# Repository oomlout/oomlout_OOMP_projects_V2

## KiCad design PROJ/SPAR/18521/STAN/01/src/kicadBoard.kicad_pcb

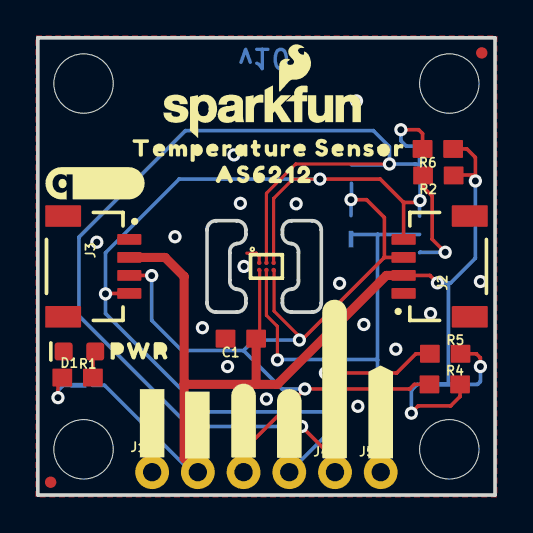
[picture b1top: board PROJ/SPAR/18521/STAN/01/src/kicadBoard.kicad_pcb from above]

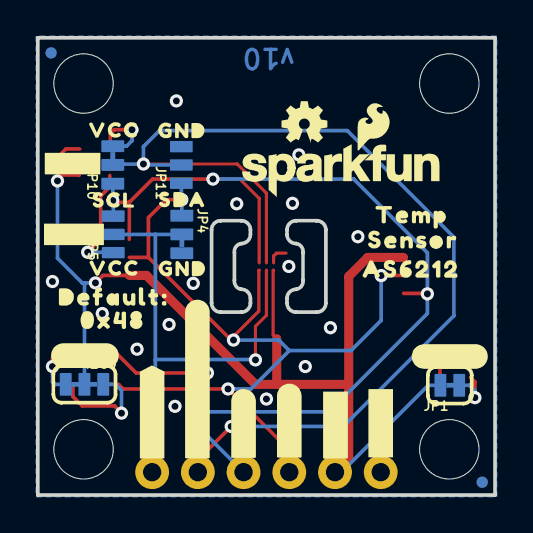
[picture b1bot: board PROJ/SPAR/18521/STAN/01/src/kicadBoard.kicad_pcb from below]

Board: 2 copper layers, 25.4 x 25.4 mm, 62 parts (31 on the bottom side), 12 nets.

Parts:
C1: 0.1uF; 0603
D1: RED; LED-0603
FD1, FD2, FD3, FD4: FIDUCIALUFIDUCIAL; FIDUCIAL-MICRO
FRAME1: FRAME-LETTER; CREATIVE_COMMONS
I2C0: SMT-JUMPER_3_2-NC_TRACE_SILK
J1: PTH; 1X04_NO_SILK
J2, J3: QWIIC_RA; JST04_1MM_RA
J4, J5: 1X01_NO_SILK
JP1: LED; SMT-JUMPER_2_NC_TRACE_SILK
JP2, JP3, JP8, JP9: STAND-OFF
JP4, JP10: JUMPER-SMT_3_1-NC_TRACE_NO-SILK; SMT-JUMPER_3_1-NC_TRACE_NO-SILK
JP5, JP11: JUMPER-SMT_3_NO_NO_SILK; SMT-JUMPER_3_0-NO_TRACE_NO-SILK
LOGO1: OSHW-LOGOMINI; OSHW-LOGO-MINI
LOGO2, LOGO4: SFE_LOGO_NAME_FLAME.1_INCH; SFE_LOGO_NAME_FLAME_.1
R1: 1k; 0603
R2, R6: 10k; 0603
R4, R5: 2.2k; 0603
U2: AS6212; WLCSP
U$1: #LED#10
U$2: #I2C#11
U$3, U$25: AS62128
U$4: #AD0#1
U$5: #AD1#1
U$6: SCL3
U$7, U$13: VCC4
U$8: DEFAULT#11
U$9, U$14: GND5
U$10: SDA6
U$11, U$12: #ALRT#AD1#12
U$15: QWIIC_5.5MM
U$16: SENSOR8
U$17: TEMP9
U$18: 0X4812
U$19: PWR12
U$20, U$21: #3V3#13
U$24: TEMPERATURE_SENSOR7
U$26, U$30: #GND#62130
U$28, U$34: #SDA#62131
U$29, U$35: #SCL#62132
U$31, U$36: #ADD0#0

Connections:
3.3V: C1.1, I2C0.2, J1.2, J2.2, J3.2, JP1.2, R2.1, R6.1, U2.B1
ADD0: J5.1, JP4.2, JP5.2, U2.B2
ALERT/ADD1: J4.1, JP10.2, JP11.2, U2.A2
GND: C1.2, D1.C, J1.1, J2.1, J3.1, JP4.3, JP11.3, U2.A1
unnamed: D1.A, R1.2
unnamed: I2C0.1, R5.2
unnamed: I2C0.3, R4.2
unnamed: JP10.3, R6.2
unnamed: JP5.1, R2.2
unnamed: JP1.1, R1.1
SCL: J1.4, J2.4, J3.4, JP5.3, JP10.1, R5.1, U2.A3
SDA: J1.3, J2.3, J3.3, JP4.1, JP11.1, R4.1, U2.B3

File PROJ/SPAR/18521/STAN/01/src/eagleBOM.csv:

"Part";"Value";"Device";"Package";"Description";"PROD_ID";"VALUE";
"C1";"0.1uF";"0.1UF-0603-25V-(+80/-20%)";"0603";"0.1µF ceramic capacitors";"CAP-00810";"0.1uF";
"D1";"RED";"LED-RED0603";"LED-0603";"Red SMD LED";"DIO-00819";"RED";
"FD1";"FIDUCIALUFIDUCIAL";"FIDUCIALUFIDUCIAL";"FIDUCIAL-MICRO";"Fiducial Alignment Points";"";"";
"FD2";"FIDUCIALUFIDUCIAL";"FIDUCIALUFIDUCIAL";"FIDUCIAL-MICRO";"Fiducial Alignment Points";"";"";
"FD3";"FIDUCIALUFIDUCIAL";"FIDUCIALUFIDUCIAL";"FIDUCIAL-MICRO";"Fiducial Alignment Points";"";"";
"FD4";"FIDUCIALUFIDUCIAL";"FIDUCIALUFIDUCIAL";"FIDUCIAL-MICRO";"Fiducial Alignment Points";"";"";
"FRAME1";"FRAME-LETTER";"FRAME-LETTER";"CREATIVE_COMMONS";"Schematic Frame - Letter";"";"";
"I2C";"";"JUMPER-SMT_3_2-NC_TRACE_SILK";"SMT-JUMPER_3_2-NC_TRACE_SILK";"Normally closed trace jumper (2 of 2 connections)";"";"";
"J1";"PTH";"I2C_STANDARD_NO_SILK";"1X04_NO_SILK";"SparkFun I2C Standard Pinout Header";"";"";
"J2";"QWIIC_RA";"QWIIC_CONNECTORJS-1MM";"JST04_1MM_RA";"SparkFun I2C Standard Qwiic Connector";"CONN-13694";"QWIIC_RIGHT_ANGLE";
"J3";"QWIIC_RA";"QWIIC_CONNECTORJS-1MM";"JST04_1MM_RA";"SparkFun I2C Standard Qwiic Connector";"CONN-13694";"QWIIC_RIGHT_ANGLE";
"J4";"";"CONN_01PTH_NO_SILK_YES_STOP";"1X01_NO_SILK";"Single connection point. Often used as Generic Header-pin footprint for 0.1 inch spaced/style header connections";"";"";
"J5";"";"CONN_01PTH_NO_SILK_YES_STOP";"1X01_NO_SILK";"Single connection point. Often used as Generic Header-pin footprint for 0.1 inch spaced/style header connections";"";"";
"JP1";"LED";"JUMPER-SMT_2_NC_TRACE_SILK";"SMT-JUMPER_2_NC_TRACE_SILK";"Normally closed trace jumper";"";"";
"JP2";"STAND-OFF";"STAND-OFF";"STAND-OFF";"Stand Off";"";"";
"JP3";"STAND-OFF";"STAND-OFF";"STAND-OFF";"Stand Off";"";"";
"JP4";"JUMPER-SMT_3_1-NC_TRACE_NO-SILK";"JUMPER-SMT_3_1-NC_TRACE_NO-SILK";"SMT-JUMPER_3_1-NC_TRACE_NO-SILK";"Normally closed trace jumper (1 of 2 connections)";"";"";
"JP5";"JUMPER-SMT_3_NO_NO_SILK";"JUMPER-SMT_3_NO_NO_SILK";"SMT-JUMPER_3_0-NO_TRACE_NO-SILK";"Normally open jumper";"";"";
"JP8";"STAND-OFF";"STAND-OFF";"STAND-OFF";"Stand Off";"";"";
"JP9";"STAND-OFF";"STAND-OFF";"STAND-OFF";"Stand Off";"";"";
"JP10";"JUMPER-SMT_3_1-NC_TRACE_NO-SILK";"JUMPER-SMT_3_1-NC_TRACE_NO-SILK";"SMT-JUMPER_3_1-NC_TRACE_NO-SILK";"Normally closed trace jumper (1 of 2 connections)";"";"";
"JP11";"JUMPER-SMT_3_NO_NO_SILK";"JUMPER-SMT_3_NO_NO_SILK";"SMT-JUMPER_3_0-NO_TRACE_NO-SILK";"Normally open jumper";"";"";
"LOGO1";"OSHW-LOGOMINI";"OSHW-LOGOMINI";"OSHW-LOGO-MINI";"Open-Source Hardware (OSHW) Logo";"";"";
"LOGO4";"SFE_LOGO_NAME_FLAME.1_INCH";"SFE_LOGO_NAME_FLAME.1_INCH";"SFE_LOGO_NAME_FLAME_.1";"SparkFun Font Logo w/ Flame";"";"";
"R1";"1k";"1KOHM-0603-1/10W-1%";"0603";"1kΩ resistor";"RES-07856";"1k";
"R2";"10k";"10KOHM-0603-1/10W-1%";"0603";"10kΩ resistor";"RES-00824";"10k";
"R4";"2.2k";"2.2KOHM-0603-1/10W-1%";"0603";"2.2kΩ resistor";"RES-08272";"2.2k";
"R5";"2.2k";"2.2KOHM-0603-1/10W-1%";"0603";"2.2kΩ resistor";"RES-08272";"2.2k";
"R6";"10k";"10KOHM-0603-1/10W-1%";"0603";"10kΩ resistor";"RES-00824";"10k";
"U2";"AS6212";"AS6212WLCSP";"WLCSP";"AMS AS6212 Low-Power Digital Temperature Sensor";"IC-16171";"AS6212";

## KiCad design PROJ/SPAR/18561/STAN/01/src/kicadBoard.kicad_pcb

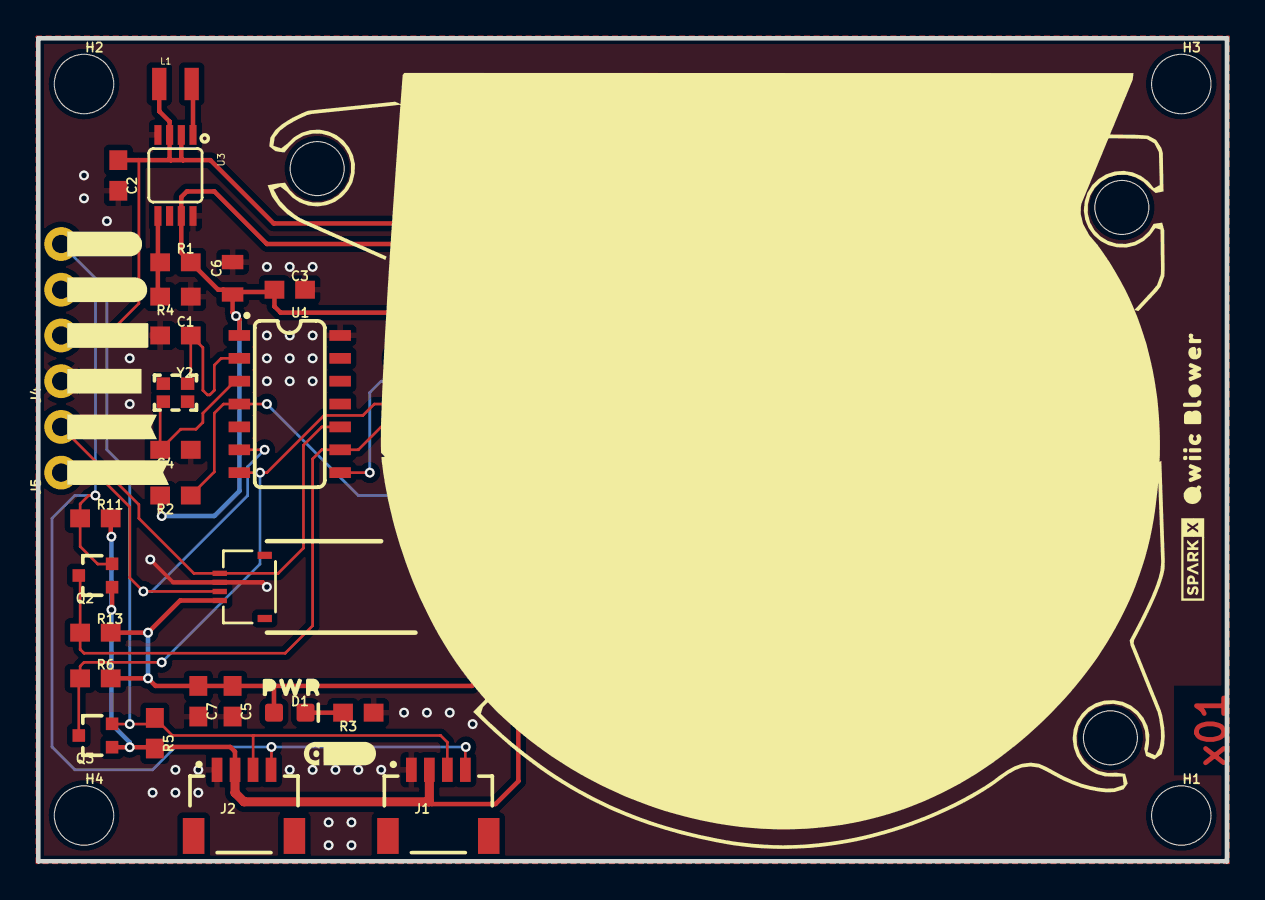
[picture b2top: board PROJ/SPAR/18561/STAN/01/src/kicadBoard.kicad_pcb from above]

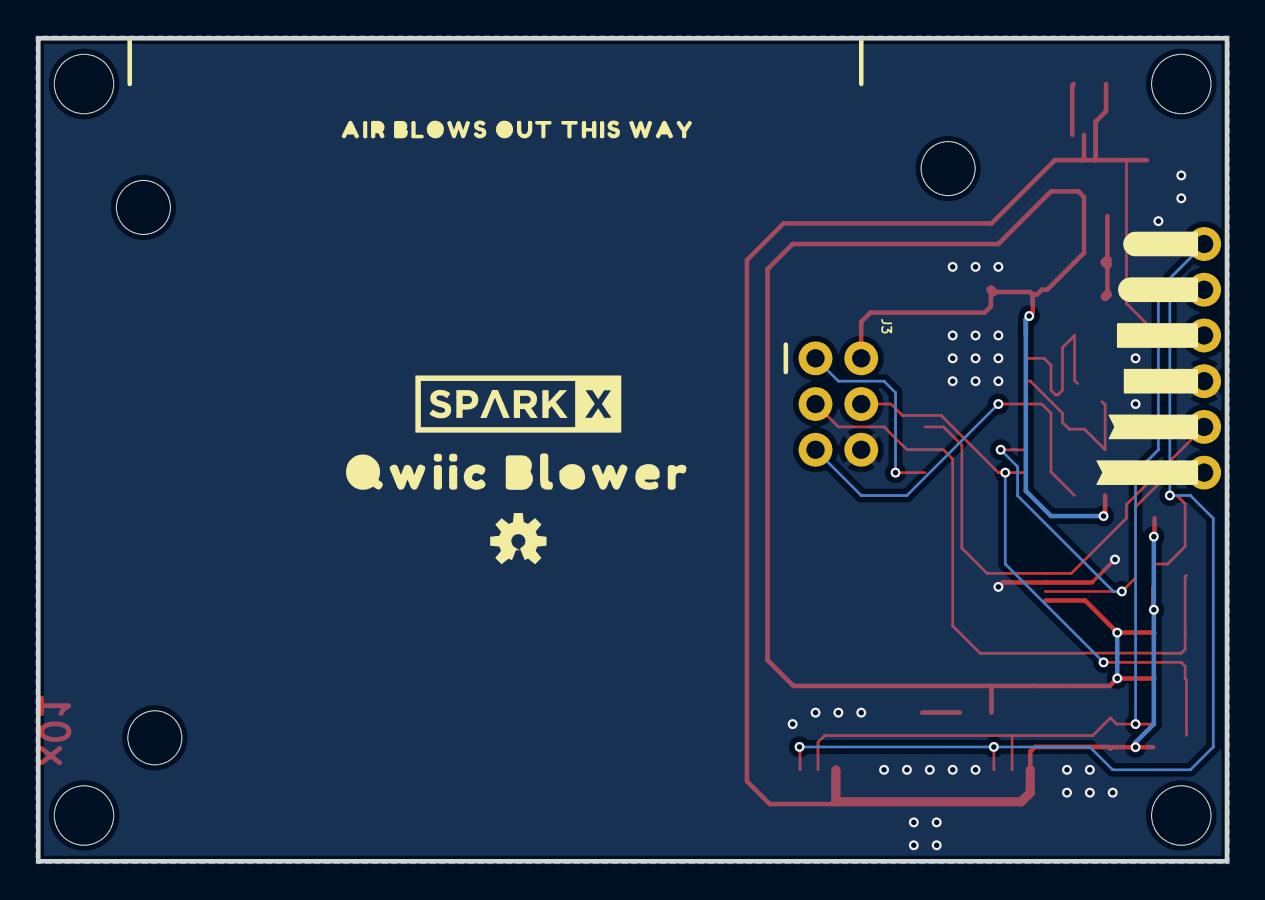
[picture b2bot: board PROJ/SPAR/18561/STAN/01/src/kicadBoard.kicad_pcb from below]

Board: 2 copper layers, 66.0 x 45.7 mm, 53 parts (11 on the bottom side), 16 nets.

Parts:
C1, C4: 22pF; 0603
C2: 10uF; 0603
C3, C5: 0.1uF; 0603
C6: 22uF; 0805
C7: 1.0uF; 0603
D1: RED; LED-0603
FRAME1: FRAME-LETTER; CREATIVE_COMMONS
H1, H2, H3, H4: STAND-OFF
J1, J2: QWIIC_RIGHT_ANGLE; JST04_1MM_RA
J3: AVR_SPI_PROG_3X2NS; 2X3-NS
J4: 1X04_NO_SILK
J5: 1X02_NO_SILK
L1: 2.2μH; 0806
Q2, Q3: 310mA/60V/1.6Ω; SOT323
R1: 750K; 0603
R2: 10k; 0603
R3: 1k; 0603
R4: 100k; 0603
R5, R6, R11, R13: 2.2k; 0603
U1: ATtiny841; SO14
U3: PAM2401; MSOP8
U$1: #_TACH#0
U$2: #_PWM#0
U$3: #_GND#0
U$4: #_3#3V#0
U$5: #_SDA#0
U$6: #_SCL#0
U$7: #SCL_#0
U$8: #SDA_#0
U$9: #3#3V_#0
U$10: #GND_#0
U$11: #PWM_#0
U$12: #TACH_#0
U$13: QWIIC_4MM
U$14: QWIIC_BLOWER0
U$15: SPARKX-TINY
U$16: AIR_BLOWS_OUT_THIS_WAY0
U$17: _QWIIC_BLOWER_0
U$18: SPARKX-LARGE
U$19: NINTENDO_SWITCH_FAN; FPC_4_0.5MM
U$20: OSHW-LOGO-S
U$21: PWR0
Y2: 16MHz; CRYSTAL-SMD-2.0X1.6MM

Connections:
3.3V: C2.1, J1.2, J2.2, J4.2, L1.1, Q2.1, Q3.1, R5.2, R11.2, U3.2, U3.3
5V: C3.1, C5.1, C6.1, C7.1, D1.A, J3.2, R1.2, R2.2, R6.2, R13.2, U1.1, U3.7, U$19.1
25KHZ_PWM: J5.2, U1.10, U$19.4
CIPO: J3.1, U1.8
FAN_TACH: J5.1, U1.6, U$19.2
GND: C1.1, C2.2, C3.2, C4.1, C5.2, C6.2, C7.2, J1.1, J2.1, J3.6, J4.1, R3.1, R4.1, U1.14, U3.4, U3.8, U$19.3
HV_SCL: J3.3, Q2.3, R13.1, U1.9
HV_SDA: J3.4, Q3.3, R6.1, U1.7
unnamed: C4.2, U1.3, Y2.1
unnamed: R1.1, R4.2, U3.5
unnamed: L1.2, U3.1
unnamed: C1.2, U1.2, Y2.3
unnamed: D1.C, R3.2
SCL: J1.4, J2.4, J4.4, Q2.2, R11.1
SDA: J1.3, J2.3, J4.3, Q3.2, R5.1
~RST: J3.5, R2.1, U1.4

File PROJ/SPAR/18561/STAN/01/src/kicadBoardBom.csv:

"Id";"Designator";"Package";"Quantity";"Designation";"Supplier and ref";
1;"R3";"0603";1;"1k";;;
2;"C6";"0805";1;"22uF";;;
3;"H3,H4,H2,H1";"STAND-OFF";4;"STAND-OFF";;;
4;"R5,R6,R11,R13";"0603";4;"2.2k";;;
5;"D1";"LED-0603";1;"RED";;;
6;"U$5";"#_SDA#0";1;"";;;
7;"C3,C5";"0603";2;"0.1uF";;;
8;"Q2,Q3";"SOT323";2;"310mA/60V/1.6Ω";;;
9;"Y2";"CRYSTAL-SMD-2.0X1.6MM";1;"16MHz";;;
10;"C2";"0603";1;"10uF";;;
11;"R1";"0603";1;"750K";;;
12;"U$6";"#_SCL#0";1;"";;;
13;"U$13";"QWIIC_4MM";1;"";;;
14;"J2,J1";"JST04_1MM_RA";2;"QWIIC_RIGHT_ANGLE";;;
15;"U$14";"QWIIC_BLOWER0";1;"";;;
16;"L1";"0806";1;"2.2μH";;;
17;"U1";"SO14";1;"ATtiny841";;;
18;"U3";"MSOP8";1;"PAM2401";;;
19;"U$15";"SPARKX-TINY";1;"";;;
20;"U$2";"#_PWM#0";1;"";;;
21;"C7";"0603";1;"1.0uF";;;
22;"C1,C4";"0603";2;"22pF";;;
23;"R4";"0603";1;"100k";;;
24;"U$1";"#_TACH#0";1;"";;;
25;"U$3";"#_GND#0";1;"";;;
26;"U$19";"FPC_4_0.5MM";1;"NINTENDO_SWITCH_FAN";;;
27;"R2";"0603";1;"10k";;;
28;"J5";"1X02_NO_SILK";1;"";;;
29;"U$4";"#_3#3V#0";1;"";;;
30;"U$21";"PWR0";1;"";;;
31;"FRAME1";"CREATIVE_COMMONS";1;"FRAME-LETTER";;;
32;"J4";"1X04_NO_SILK";1;"";;;
33;"U$9";"#3#3V_#0";1;"";;;
34;"U$12";"#TACH_#0";1;"";;;
35;"U$20";"OSHW-LOGO-S";1;"";;;
36;"J3";"2X3-NS";1;"AVR_SPI_PROG_3X2NS";;;
37;"U$10";"#GND_#0";1;"";;;
38;"U$8";"#SDA_#0";1;"";;;
39;"U$18";"SPARKX-LARGE";1;"";;;
40;"U$11";"#PWM_#0";1;"";;;
41;"U$17";"_QWIIC_BLOWER_0";1;"";;;
42;"U$16";"AIR_BLOWS_OUT_THIS_WAY0";1;"";;;
43;"U$7";"#SCL_#0";1;"";;;

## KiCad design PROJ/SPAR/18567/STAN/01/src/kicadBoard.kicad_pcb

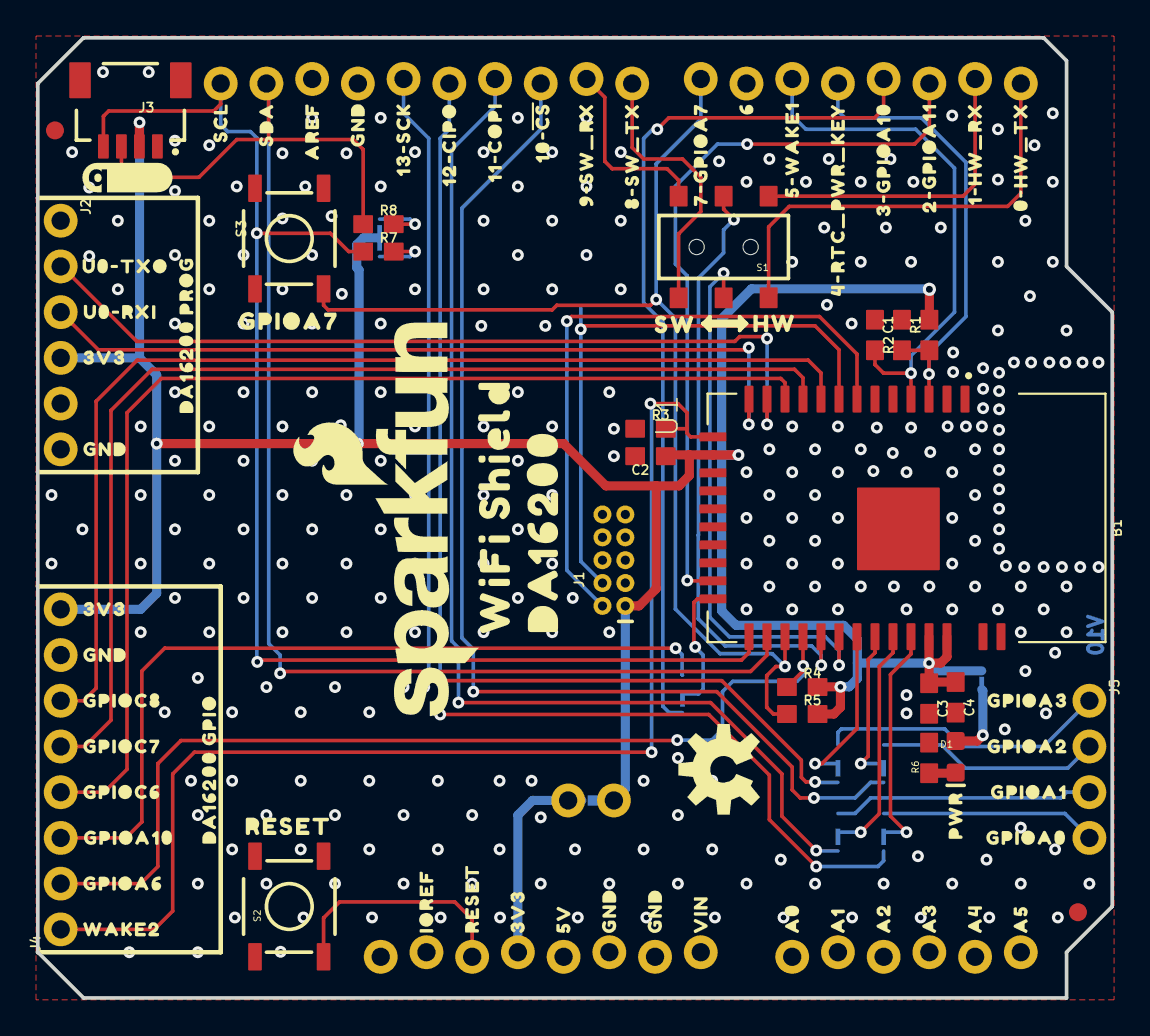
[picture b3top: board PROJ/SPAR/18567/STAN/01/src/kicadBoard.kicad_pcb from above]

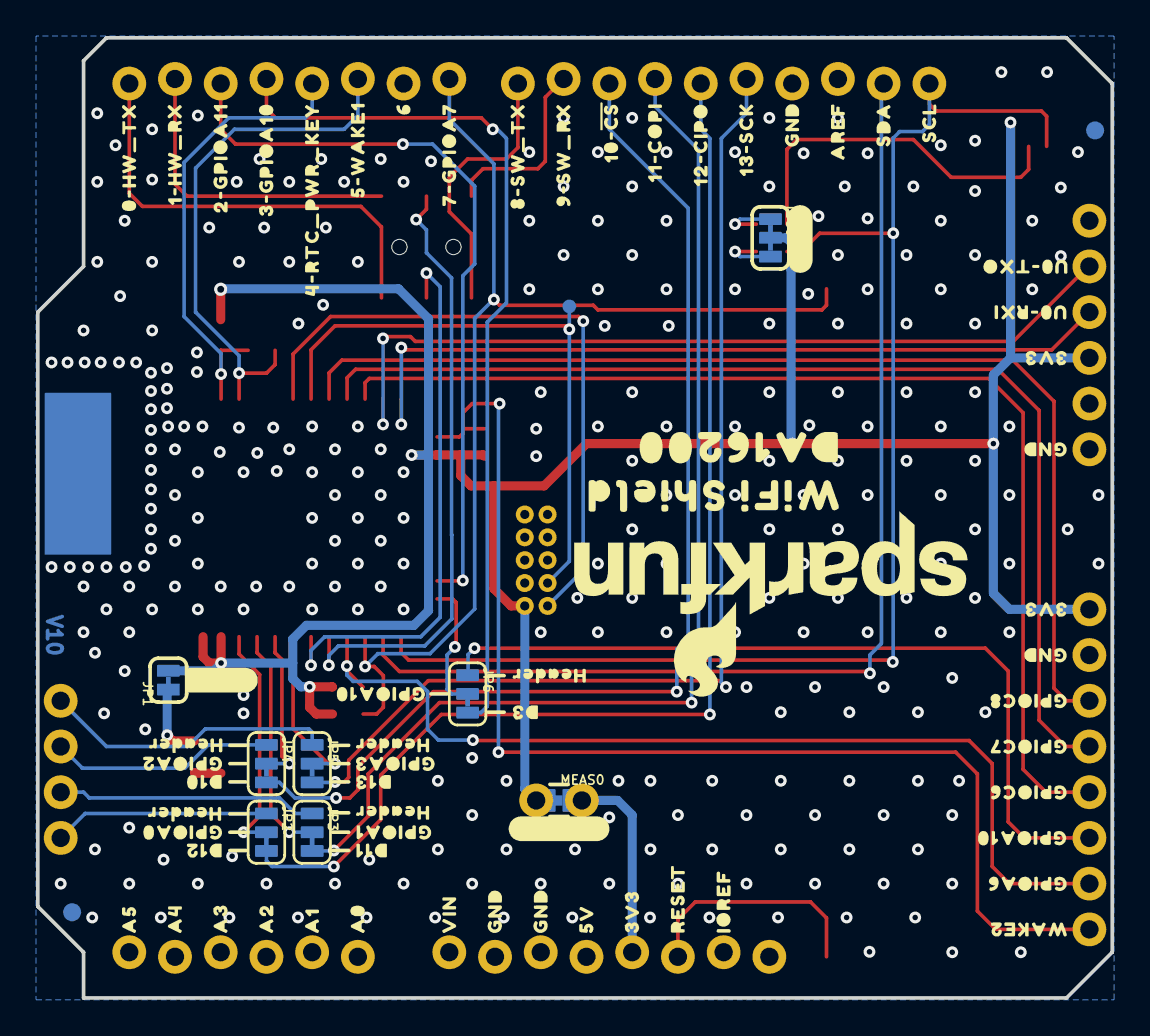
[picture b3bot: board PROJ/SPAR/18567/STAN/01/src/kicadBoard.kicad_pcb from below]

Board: 2 copper layers, 59.7 x 53.3 mm, 160 parts (75 on the bottom side), 44 nets.

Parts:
B1: ARDUINO_UNO_R3_SHIELD; UNO_R3_SHIELD_NOLABELS_LOCK
C1: DNP; 0603
C2, C3: 1uF; 0603
C4: 10uF; 0603
D1: RED; LED-0603
FD1, FD2, FD3, FD4: FIDUCIAL1X2; FIDUCIAL-1X2
FRAME1: FRAME-LETTER; CREATIVE_COMMONS
I2C0: SMT-JUMPER_3_2-NC_TRACE_SILK
J1: CORTEX_JTAG_DEBUG; 2X5-PTH-1.27MM-NO_SILK
J2: 1X06_NO_SILK
J3: QWIIC_RA; JST04_1MM_RA
J4: 1X08_NO_SILK
J5: 1X04_NO_SILK
JP1: SMT-JUMPER_2_NC_TRACE_SILK
JP2, JP3, JP4, JP5, JP6: SMT-JUMPER_3_1-NC_TRACE_SILK
LOGO1, LOGO3: SFE_LOGO_NAME_FLAME.2_INCH; SFE_LOGO_NAME_FLAME_.2
LOGO2: OSHW-LOGOM; OSHW-LOGO-M
LOGO4: QWIIC_LOGO_5MM; QWIIC_5MM
MEAS0: COMBO-JUMPER_2_NC_TRACE
R1: DNP; 0603
R2, R3, R4, R5, R7, R8: 4.7k; 0603
R6: 200; 0603
S1: DPDT; SWITCH_DPDT_SMD_AYZ0202
S2: Reset; TACTILE_SWITCH_SMD_5.2MM
S3: TACTILE_SWITCH_SMD_5.2MM
TP1: PAD.03X.03
U1: DA16200MOD; XCVR_DA16200MOD-AAC4WA32
U$1, U$16: IOREF0
U$2, U$19: RESET0
U$3, U$37, U$39, U$41, U$85, U$87: 3V30
U$4, U$55: 5V0
U$5, U$6, U$28, U$40, U$52, U$56, U$57, U$79, U$86, U$88: GND0
U$7, U$58: VIN0
U$8, U$59: A00
U$9, U$60: A10
U$10, U$61: A20
U$11, U$62: A30
U$12, U$63: A40
U$13, U$64: A50
U$14, U$65: 0#HW_TX0
U$15, U$66: 1#HW_RX0
U$17, U$95: GPIOA60
U$18, U$70: 4#RTC_PWR_KEY0
U$20, U$73: 8#SW_TX0
U$21, U$72: 7#GPIOA70
U$23, U$33: 5#WAKE10
U$24, U$75: 10##CS#0
U$25, U$76: 11#COPI0
U$26, U$77: 12#CIPO0
U$27, U$78: 13#SCK0
U$29, U$80: AREF0
U$30, U$81: SDA0
U$31, U$82: SCL0
U$32, U$74: 9#SW_RX0
U$34: GPIOA70
U$35, U$48: WAKE20
U$36: RESET_0
U$38, U$71: 60
U$42: HW0
U$43: SW0
U$44, U$89: GPIOC80
U$45, U$90: GPIOC70
U$46, U$91: GPIOC60
U$47, U$69, U$92: GPIOA100
U$49: #I2C#0
U$50, U$109: 2#GPIOA110
U$51, U$68: 3#GPIOA100
U$53, U$83: U0#TXO0
U$54, U$84: U0#RXI0
U$93, U$115: GPIOA00
U$94, U$114: GPIOA10
U$96: D30
U$97: #LED#0
U$98: #MEAS#0
U$99: PWR0
U$100, U$107: WIFI_SHIELD0
U$101, U$108: DA162000
U$102, U$116: GPIOA20
U$103, U$117: GPIOA30
U$104: DA16200_GPIO0
U$105: DA16200_PROG0
U$106, U$118, U$119, U$120, U$121: HEADER0
U$122: D100
U$123: D110
U$124: D120
U$125: D130

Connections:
3.3V: C2.1, C3.1, C4.1, I2C0.2, J1.1, J2.4, J3.2, J4.8, JP1.2, MEAS0.1, MEAS0.3, R1.2, R4.2, R5.2, U1.15, U1.34, U1.35
ARD_GPIOA10: B1.D3, JP6.3
ARD_HW_RX: B1.RX, S1.1
ARD_HW_TX: B1.TX, S1.4
ARD_RESET: B1.RES, S2.3
ARD_SCL: B1.SCL, J3.4, R7.1, U1.24
ARD_SDA: B1.SDA, J3.3, R8.1, U1.25
ARD_SW_RX: B1.D8, S1.3
ARD_SW_TX: B1.D9, S1.6
GND: B1.GND@0, B1.GND@1, B1.GND@2, C1.2, C2.2, C3.2, C4.2, J1.3, J1.5, J1.9, J2.6, J3.1, J4.7, R2.1, R3.1, R6.2, S2.1, S3.1, U1.2, U1.ANT_GND, U1.GND
GPIOA0: JP2.2, U1.33
GPIOA1: JP3.2, U1.32
GPIOA2: JP4.2, U1.31
GPIOA3: JP5.2, U1.30
GPIOA7: B1.D7, R5.1, S3.3, U1.26
GPIOA10: JP6.2, U1.23
GPIOA11: B1.D2, U1.22
HDR_GPIOA0: J5.4, JP2.1
HDR_GPIOA1: J5.3, JP3.1
HDR_GPIOA2: J5.2, JP4.1
HDR_GPIOA3: J5.1, JP5.1
HDR_GPIOA6: J4.2, R4.1, U1.27
HDR_GPIOA10: J4.3, JP6.1
HDR_GPIOC6: J4.4, U1.11
HDR_GPIOC7: J4.5, U1.10
HDR_GPIOC8: J4.6, U1.9
HDR_RTC_WAKE2: J4.1, R3.2, U1.14
unnamed: B1.3.3V, MEAS0.2, MEAS0.4
unnamed: D1.A, JP1.1
unnamed: I2C0.3, R7.2
unnamed: I2C0.1, R8.2
unnamed: D1.C, R6.1
RTC_PWR_KEY: B1.D4, C1.1, R1.1, U1.3
RTC_WAKE1: B1.D5, R2.2, U1.4
SPI_CIPO: B1.D12, JP2.3
SPI_COPI: B1.D11, JP3.3
SPI_CS: B1.D10, JP4.3
SPI_SCK: B1.D13, JP5.3
TCLK: J1.4, TP1.1, U1.8
TMS: J1.2, U1.7
U0RXI: J2.3, U1.13
U0TXO: J2.2, U1.12
U1RXI: S1.5, U1.28
U1TXO: S1.2, U1.29

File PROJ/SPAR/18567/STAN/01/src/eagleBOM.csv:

"Part";"Value";"Device";"Package";"Description";"DESIGNER";"PROD_ID";"REV";"SF_SKU";"VALUE";
"B1";"ARDUINO_UNO_R3_SHIELD";"ARDUINO_UNO_R3_SHIELDUNO_R3_SHIELD_NOLABELS_LOCK";"UNO_R3_SHIELD_NOLABELS_LOCK";"Arduino R3 Shield Footprint";"";"";"";"";"";
"C1";"DNP";"CAP-0603";"0603";"";"";"";"";"";"";
"C2";"1uF";"1.0UF-0603-16V-10%";"0603";"1µF ceramic capacitors";"";"CAP-00868";"";"";"1.0uF";
"C3";"1uF";"1.0UF-0603-16V-10%";"0603";"1µF ceramic capacitors";"";"CAP-00868";"";"";"1.0uF";
"C4";"10uF";"10UF-0603-6.3V-20%";"0603";"10.0µF ceramic capacitors";"";"CAP-11015";"";"";"10uF";
"D1";"RED";"LED-RED0603";"LED-0603";"Red SMD LED";"";"DIO-00819";"";"";"RED";
"FD1";"FIDUCIAL1X2";"FIDUCIAL1X2";"FIDUCIAL-1X2";"Fiducial Alignment Points";"";"";"";"";"";
"FD2";"FIDUCIAL1X2";"FIDUCIAL1X2";"FIDUCIAL-1X2";"Fiducial Alignment Points";"";"";"";"";"";
"FD3";"FIDUCIAL1X2";"FIDUCIAL1X2";"FIDUCIAL-1X2";"Fiducial Alignment Points";"";"";"";"";"";
"FD4";"FIDUCIAL1X2";"FIDUCIAL1X2";"FIDUCIAL-1X2";"Fiducial Alignment Points";"";"";"";"";"";
"FRAME1";"FRAME-LETTER";"FRAME-LETTER";"CREATIVE_COMMONS";"Schematic Frame - Letter";"";"";"";"";"";
"I2C";"";"JUMPER-SMT_3_2-NC_TRACE_SILK";"SMT-JUMPER_3_2-NC_TRACE_SILK";"Normally closed trace jumper (2 of 2 connections)";"";"";"";"";"";
"J1";"CORTEX_JTAG_DEBUG";"CORTEX_JTAG_DEBUG_PTH_NS";"2X5-PTH-1.27MM-NO_SILK";"Cortex Debug Connector - 10 pin";"";"";"";"";"";
"J2";"";"6_PIN_SERIAL_TARGET_NO_SILK";"1X06_NO_SILK";"6-pin header connection for use with the "FTDI BASIC" pinout - TARGET SIDE.";"";"";"";"";"";
"J3";"QWIIC_RA";"QWIIC_CONNECTORJS-1MM";"JST04_1MM_RA";"SparkFun I2C Standard Qwiic Connector";"";"CONN-13694";"";"";"QWIIC_RIGHT_ANGLE";
"J4";"";"CONN_08NO_SILK_DNP";"1X08_NO_SILK";"Multi connection point. Often used as Generic Header-pin footprint for 0.1 inch spaced/style header connections";"";"";"";"";"";
"J5";"";"CONN_041X04_NO_SILK";"1X04_NO_SILK";"Multi connection point. Often used as Generic Header-pin footprint for 0.1 inch spaced/style header connections";"";"CONN-09696";"";"";"";
"JP1";"";"JUMPER-SMT_2_NC_TRACE_SILK";"SMT-JUMPER_2_NC_TRACE_SILK";"Normally closed trace jumper";"";"";"";"";"";
"JP2";"";"JUMPER-SMT_3_1-NC_TRACE_SILK";"SMT-JUMPER_3_1-NC_TRACE_SILK";"Normally closed trace jumper (1 of 2 connections)";"";"";"";"";"";
"JP3";"";"JUMPER-SMT_3_1-NC_TRACE_SILK";"SMT-JUMPER_3_1-NC_TRACE_SILK";"Normally closed trace jumper (1 of 2 connections)";"";"";"";"";"";
"JP4";"";"JUMPER-SMT_3_1-NC_TRACE_SILK";"SMT-JUMPER_3_1-NC_TRACE_SILK";"Normally closed trace jumper (1 of 2 connections)";"";"";"";"";"";
"JP5";"";"JUMPER-SMT_3_1-NC_TRACE_SILK";"SMT-JUMPER_3_1-NC_TRACE_SILK";"Normally closed trace jumper (1 of 2 connections)";"";"";"";"";"";
"JP6";"";"JUMPER-SMT_3_1-NC_TRACE_SILK";"SMT-JUMPER_3_1-NC_TRACE_SILK";"Normally closed trace jumper (1 of 2 connections)";"";"";"";"";"";
"LOGO1";"SFE_LOGO_NAME_FLAME.2_INCH";"SFE_LOGO_NAME_FLAME.2_INCH";"SFE_LOGO_NAME_FLAME_.2";"SparkFun Font Logo w/ Flame";"";"";"";"";"";
"LOGO2";"OSHW-LOGOM";"OSHW-LOGOM";"OSHW-LOGO-M";"Open-Source Hardware (OSHW) Logo";"";"";"";"";"";
"LOGO4";"QWIIC_LOGO_5MM";"QWIIC_LOGO_5MM";"QWIIC_5MM";"Qwiic Logos for placement on schematic and PCB. The 5.5mm silk logo is best for placing next to Qwiic connector.";"";"";"";"";"";
"MEAS";"";"JUMPER-COMBO_2_NC_TRACE";"COMBO-JUMPER_2_NC_TRACE";"";"";"";"";"";"";
"R1";"DNP";"RESISTOR0603";"0603";"Generic Resistor Package";"";" ";"";"";" ";
"R2";"4.7k";"4.7KOHM-0603-1/10W-1%";"0603";"4.7kΩ resistor";"";"RES-07857";"";"";"4.7k";
"R3";"4.7k";"4.7KOHM-0603-1/10W-1%";"0603";"4.7kΩ resistor";"";"RES-07857";"";"";"4.7k";
"R4";"4.7k";"4.7KOHM-0603-1/10W-1%";"0603";"4.7kΩ resistor";"";"RES-07857";"";"";"4.7k";
"R5";"4.7k";"4.7KOHM-0603-1/10W-1%";"0603";"4.7kΩ resistor";"";"RES-07857";"";"";"4.7k";
"R6";"200";"200OHM-0603-1/10W-1%";"0603";"200Ω resistor";"";"RES-08220";"";"";"200";
"R7";"4.7k";"4.7KOHM-0603-1/10W-1%";"0603";"4.7kΩ resistor";"";"RES-07857";"";"";"4.7k";
"R8";"4.7k";"4.7KOHM-0603-1/10W-1%";"0603";"4.7kΩ resistor";"";"RES-07857";"";"";"4.7k";
"S1";"DPDT";"SWITCH-DPDT-SMD-AYZ0202";"SWITCH_DPDT_SMD_AYZ0202";"Double-Pole, Double-Throw (DPDT) Switch";"";"SWCH-08179";"";"COM-00597";"";
"S2";"Reset";"MOMENTARY-SWITCH-SPST-SMD-5.2MM-TALL";"TACTILE_SWITCH_SMD_5.2MM";"Momentary Switch (Pushbutton) - SPST";"";"SWCH-14139";"";"";"";
"S3";"";"MOMENTARY-SWITCH-SPST-SMD-5.2MM-TALL";"TACTILE_SWITCH_SMD_5.2MM";"Momentary Switch (Pushbutton) - SPST";"";"SWCH-14139";"";"";"";
"TP1";"";"TEST-POINT3";"PAD.03X.03";"SparkFun Test Points";"";"";"";"";"";
"U1";"DA16200MOD";"DA16200MOD-AAC4WA32";"XCVR_DA16200MOD-AAC4WA32";"Check prices";"";"IC-16179";"";"";"DA16200MOD";

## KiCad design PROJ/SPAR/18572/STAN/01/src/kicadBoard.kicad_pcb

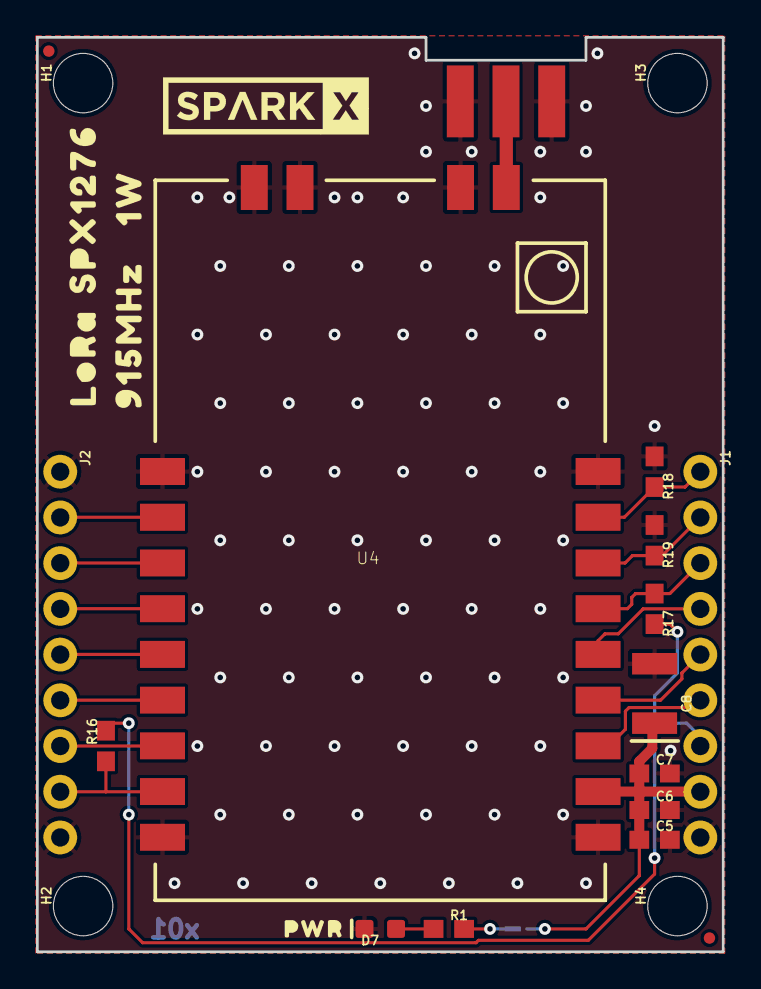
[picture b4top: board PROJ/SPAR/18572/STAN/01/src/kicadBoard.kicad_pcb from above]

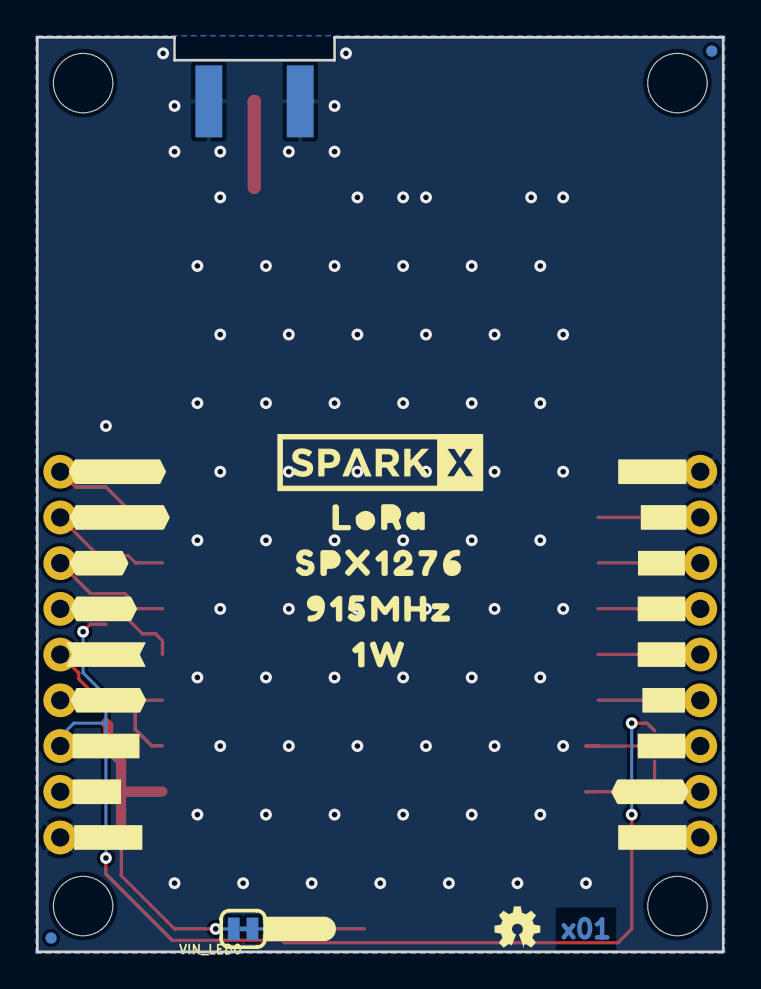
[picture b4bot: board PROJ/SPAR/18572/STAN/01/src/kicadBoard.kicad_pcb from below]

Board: 2 copper layers, 38.1 x 50.8 mm, 55 parts (28 on the bottom side), 19 nets.

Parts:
C5: 1.0uF; 0603
C6: 0.1uF; 0603
C7: 0.22uF; 0603
C8: 47uF; EIA3528
D7: Yellow; LED-0603
E1: RP-SMA; SMA-EDGE
FD1, FD2, FD3, FD4: FIDUCIALUFIDUCIAL; FIDUCIAL-MICRO
FRAME2: FRAME-LETTER; CREATIVE_COMMONS
H1, H2, H3, H4: STAND-OFF
J1, J2: 1X09_NO_SILK
LOGO3: OSHW-LOGOMINI; OSHW-LOGO-MINI
R1: 1k; 0603
R16, R17, R18, R19: 100k; 0603
U4: E19-915M30S; E19-915MS1W
U$1, U$67: LORA0
U$2, U$69: SPX12760
U$3, U$27: 1W1
U$4: PWR0
U$5, U$6: SPARKX-LOGO5; SPARKX-LARGE
U$7, U$8: 915MHZ0
U$15: #LED#0
U$43: #5V#1
U$44: #3V3#0
U$45: #SDO#3
U$46: #SDI#4
U$47: ##CS##5
U$48: #TXEN#6
U$49: #RXEN#7
U$52, U$53, U$61: #GND#8
U$54: #D5#6
U$55: #D4#5
U$56: #D3#4
U$57: #D2#3
U$58: #D1#2
U$59: #D0#1
U$60: ##RST##0
U$62: #SCK#2
VIN_LED0: SMT-JUMPER_2_NC_TRACE_SILK

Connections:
3.3V: J1.7, R16.2, R17.2
5V: C5.1, C6.1, C7.1, C8.A, J1.8, U4.11, VIN_LED0.2
GND: C5.2, C6.2, C7.2, C8.C, D7.C, E1.GND@0, E1.GND@1, E1.GND@2, E1.GND@3, J1.9, J2.1, J2.9, R18.1, R19.1, U4.1, U4.9, U4.10, U4.18, U4.20, U4.21, U4.22
LORA_CIPO: J1.5, U4.13
LORA_COPI: J1.4, U4.14
LORA_D0: J2.7, U4.7
LORA_D1: J2.6, U4.6
LORA_D2: J2.5, U4.5
LORA_D3: J2.4, U4.4
LORA_D4: J2.3, U4.3
LORA_D5: J2.2, U4.2
LORA_RF: E1.SIG, U4.19
LORA_RXEN: J1.1, R18.2, U4.17
LORA_SCK: J1.6, U4.12
LORA_TXEN: J1.2, R19.2, U4.16
LORA_~CS: J1.3, R17.1, U4.15
LORA_~RST: J2.8, R16.1, U4.8
unnamed: R1.2, VIN_LED0.1
unnamed: D7.A, R1.1

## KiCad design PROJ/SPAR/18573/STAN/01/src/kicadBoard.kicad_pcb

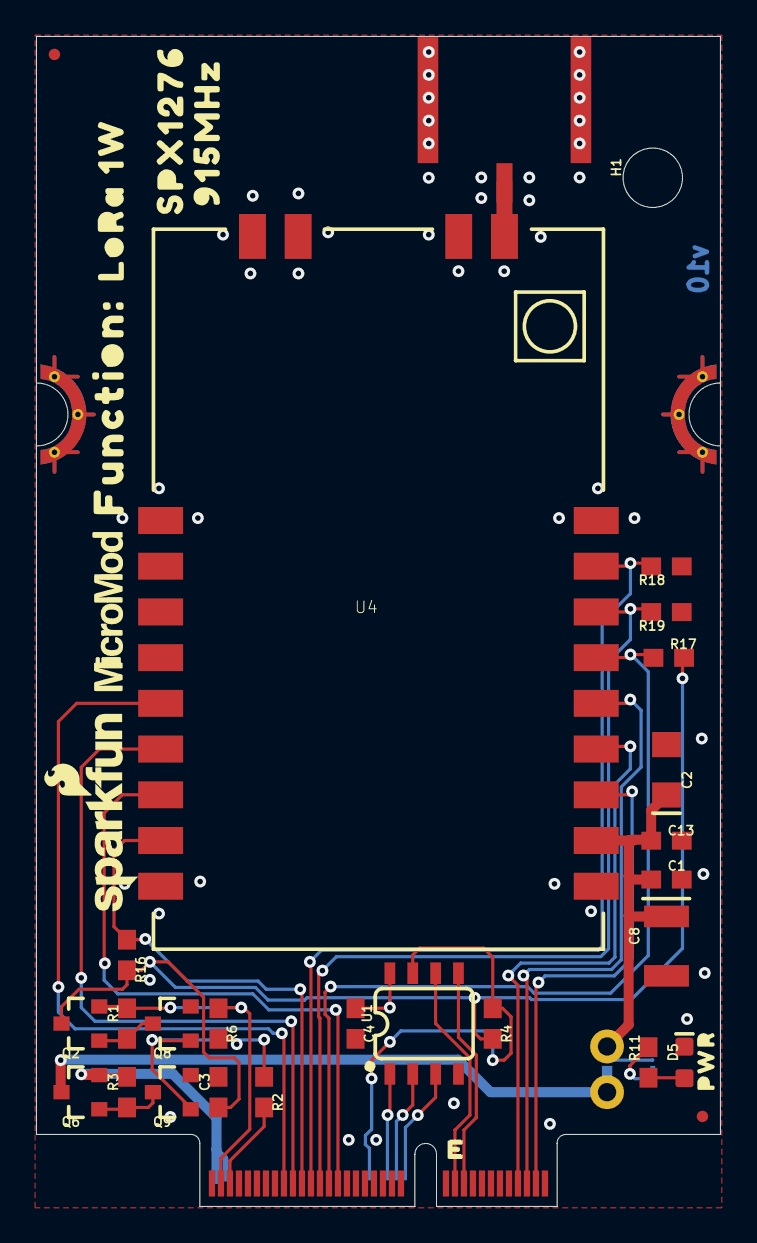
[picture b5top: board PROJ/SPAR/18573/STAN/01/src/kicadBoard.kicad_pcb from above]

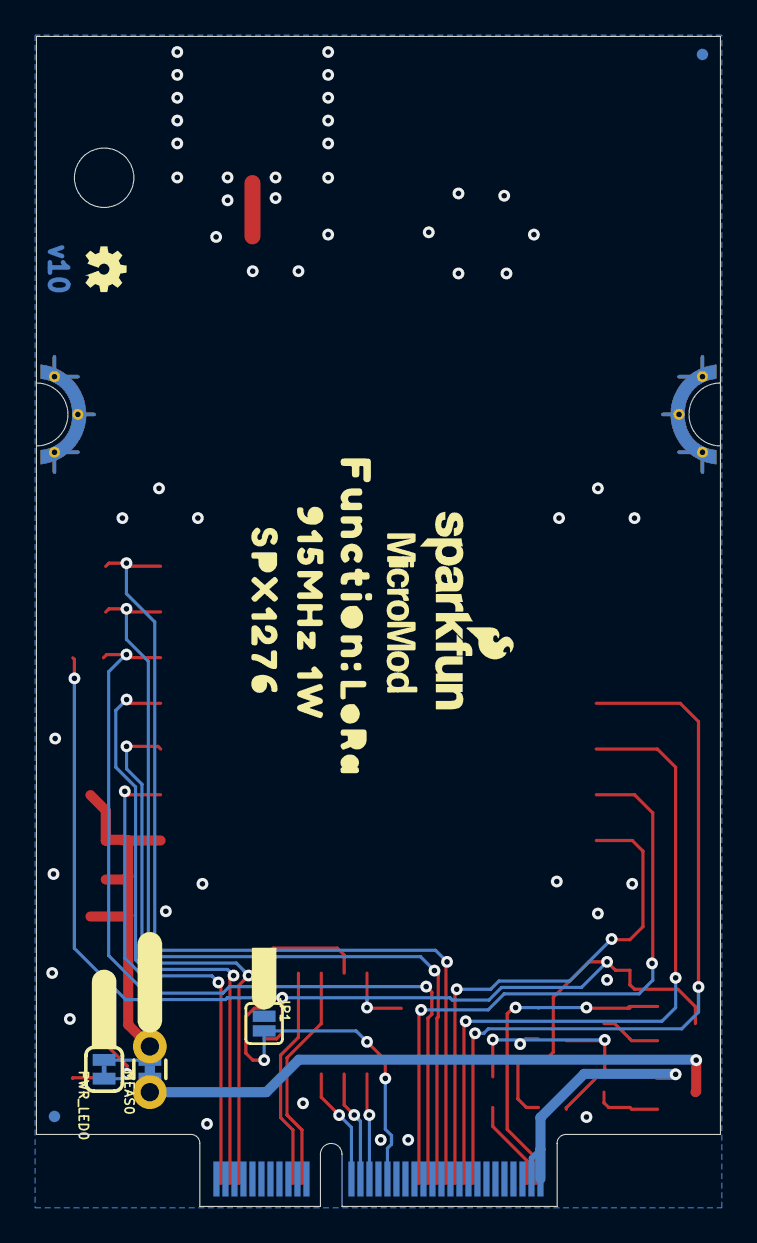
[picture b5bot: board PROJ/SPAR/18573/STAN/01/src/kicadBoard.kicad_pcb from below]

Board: 2 copper layers, 38.0 x 65.0 mm, 54 parts (16 on the bottom side), 29 nets.

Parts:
C1, C3, C4: 0.1uF; 0603
C2: 10uF; EIA3216
C8: 47uF; EIA3528
C13: 0.22uF; 0603
D5: RED; LED-0603
E1: RP-SMA; SMA-EDGE-SMD
FD1, FD2, FD3, FD4: FIDUCIALUFIDUCIAL; FIDUCIAL-MICRO
FRAME2: FRAME-LETTER; CREATIVE_COMMONS
H1: STAND-OFF
J11: MICROMOD_FUNCTION_STANDARD; M.2-CARD-E-22_FUNCTION_STANDARD
JP1: JUMPER-SMT_2_NO_SILK; SMT-JUMPER_2_NO_SILK
LOGO1, LOGO4: SFE_LOGO_NAME_FLAME.1_INCH; SFE_LOGO_NAME_FLAME_.1
LOGO2: SPECIAL_INSTRUCTIONS-ORDERING; ORDERING_INSTRUCTIONS
LOGO3: OSHW-LOGOMINI; OSHW-LOGO-MINI
MEAS0: JUMPER-COMBO_2_NC_TRACE; COMBO-JUMPER_2_NC_TRACE
PWR_LED0: JUMPER-SMT_2_NC_TRACE_SILK; SMT-JUMPER_2_NC_TRACE_SILK
Q2, Q6: 20V/4.2A/52mΩ/1.4W; SOT23-3
Q8, Q9: 5.8A/30V/35mΩ; SOT23-3
R1, R3, R4: 10k; 0603
R2: 470; 0603
R6, R16, R17, R18, R19: 100k; 0603
R11: 1k; 0603
U1: EEPROM; SO08
U4: E19-915M30S; E19-915MS1W
U$1, U$5: LORA0
U$2, U$30: 1W1
U$3, U$29: 915MHZ2
U$4, U$8: FUNCTION#0
U$6, U$27: SPX12763
U$7: PWR0
U$9: #PWR#0
U$10: #WP#0
U$28: #MEAS#3
U$37, U$63: MICROMOD_LOGO_.35

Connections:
3.3V: C3.1, C4.1, Q2.3, R4.2, R16.2, R17.2, U1.8
3.3V_IN: J11.73, Q2.2, R1.2, R6.1
5V: C1.1, C2.+, C8.A, C13.1, MEAS0.2, MEAS0.4, PWR_LED0.2, U4.11
A0: J11.36, U1.1
A1: J11.34, U1.2
A2: J11.32, U1.3
EWP: J11.40, JP1.2, R4.1, U1.7
GND: C1.2, C2.-, C3.2, C4.2, C8.C, C13.2, D5.C, E1.GND@0, E1.GND@1, J11.1, J11.33, J11.39, J11.45, J11.75, J11.GND1, J11.GND2, J11.GND3, J11.GND4, J11.GND5, J11.GND6, JP1.1, Q8.2, Q9.2, R18.1, R19.1, U1.4, U4.1, U4.9, U4.10, U4.18, U4.20, U4.21, U4.22
I2C_SCL: J11.21, U1.6
I2C_SDA: J11.19, U1.5
LORA_D0: J11.47, U4.7
LORA_D1: J11.57, U4.6
LORA_D2: J11.59, U4.5
LORA_RXEN: J11.53, R18.2, U4.17
LORA_TXEN: J11.51, R19.2, U4.16
LORA_~CS: J11.49, R17.1, U4.15
LORA_~RST: J11.55, R16.1, U4.8
unnamed: E1.SIG, U4.19
unnamed: Q2.1, Q8.3, R1.1
unnamed: Q6.1, Q9.3, R3.1
unnamed: J11.71, R2.2
unnamed: D5.A, R11.1
unnamed: PWR_LED0.1, R11.2
PWR_EN: Q8.1, Q9.1, R2.1, R6.2
SPI_CIPO: J11.7, U4.13
SPI_COPI: J11.5, U4.14
SPI_SCK: J11.3, U4.12
VCC: MEAS0.1, MEAS0.3, Q6.3
VCC_IN: J11.72, J11.74, Q6.2, R3.2

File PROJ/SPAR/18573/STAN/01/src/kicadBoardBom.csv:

"Id";"Designator";"Package";"Quantity";"Designation";"Supplier and ref";
1;"U$7";"PWR0";1;"";;;
2;"H1";"STAND-OFF";1;"STAND-OFF";;;
3;"U$63,U$37";"MICROMOD_LOGO_.35";2;"";;;
4;"R19,R17,R16,R6,R18";"0603";5;"100k";;;
5;"U4";"E19-915MS1W";1;"E19-915M30S";;;
6;"U$5,U$1";"LORA0";2;"";;;
7;"LOGO2";"ORDERING_INSTRUCTIONS";1;"SPECIAL_INSTRUCTIONS-ORDERING";;;
8;"LOGO1,LOGO4";"SFE_LOGO_NAME_FLAME_.1";2;"SFE_LOGO_NAME_FLAME.1_INCH";;;
9;"R4,R3,R1";"0603";3;"10k";;;
10;"R11";"0603";1;"1k";;;
11;"U$6,U$27";"SPX12763";2;"";;;
12;"U$8,U$4";"FUNCTION#0";2;"";;;
13;"Q8,Q9";"SOT23-3";2;"5.8A/30V/35mΩ";;;
14;"C3,C1,C4";"0603";3;"0.1uF";;;
15;"FD2,FD1,FD3,FD4";"FIDUCIAL-MICRO";4;"FIDUCIALUFIDUCIAL";;;
16;"Q2,Q6";"SOT23-3";2;"20V/4.2A/52mΩ/1.4W";;;
17;"E1";"SMA-EDGE-SMD";1;"RP-SMA";;;
18;"J11";"M.2-CARD-E-22_FUNCTION_STANDARD";1;"MICROMOD_FUNCTION_STANDARD";;;
19;"R2";"0603";1;"470";;;
20;"D5";"LED-0603";1;"RED";;;
21;"U$2,U$30";"1W1";2;"";;;
22;"FRAME2";"CREATIVE_COMMONS";1;"FRAME-LETTER";;;
23;"U1";"SO08";1;"EEPROM";;;
24;"C13";"0603";1;"0.22uF";;;
25;"C2";"EIA3216";1;"10uF";;;
26;"C8";"EIA3528";1;"47uF";;;
27;"U$3,U$29";"915MHZ2";2;"";;;
28;"U$28";"#MEAS#3";1;"";;;
29;"U$10";"#WP#0";1;"";;;
30;"JP1";"SMT-JUMPER_2_NO_SILK";1;"JUMPER-SMT_2_NO_SILK";;;
31;"PWR_LED0";"SMT-JUMPER_2_NC_TRACE_SILK";1;"JUMPER-SMT_2_NC_TRACE_SILK";;;
32;"LOGO3";"OSHW-LOGO-MINI";1;"OSHW-LOGOMINI";;;
33;"MEAS0";"COMBO-JUMPER_2_NC_TRACE";1;"JUMPER-COMBO_2_NC_TRACE";;;
34;"U$9";"#PWR#0";1;"";;;

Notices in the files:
parts and their libraries:
RELEASED UNDER THE CREATIVE COMMONS ATTRIBUTION SHARE-ALIKE 4.0 LICENSE
HTTPS://CREATIVECOMMONS.ORG/LICENSES/BY-SA/4.0
